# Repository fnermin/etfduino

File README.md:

MATLAB and Arduino to Acquire Analog Signals +15V/+15V

etfarduino

A project which allows the use of an Arduino device for data acquisition within the MATLAB Data Acquisition Toolbox.

A zip bundle containing the compiled x86 binaries and Arduino source can be downloaded from https://github.com/mlalic/etfarduino

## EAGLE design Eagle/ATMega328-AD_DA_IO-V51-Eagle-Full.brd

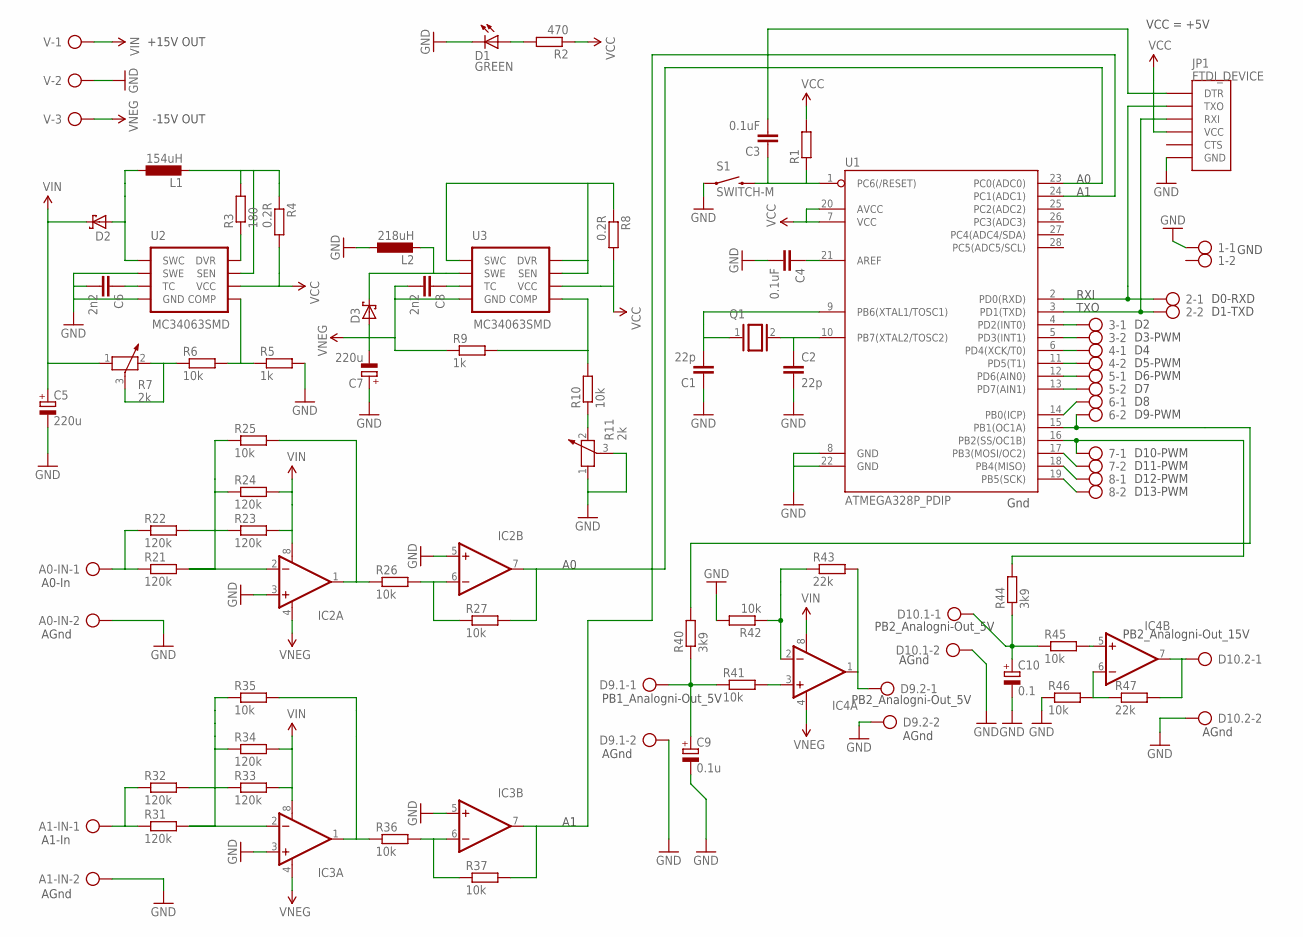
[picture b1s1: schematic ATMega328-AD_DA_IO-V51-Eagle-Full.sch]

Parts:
1, 2, 3, 4, 5, 6, 7, 8: AK500/2
A0-IN, A1-IN: AK500/2
C1, C2: 22p; C0805K
C3, C4: 0.1uF; C0805K
C5, C7: 220u; E3,5-10
C6, C8: 2n2; C0805K
C9: 0.1u; E2,5-5
C10: 0.1; E2,5-5
D1: GREEN; LED-1206
D2, D3: SCHOTTKY-DIODESMD; SMB
D9.1, D9.2, D10.1, D10.2: AK500/2
IC2, IC3, IC4: OPAMP-DUALU; SO08
JP1: FTDI_DEVICE; FTDI_DEVICE_SIDE
L1: 154uH; 0207/2V
L2: 218uH; 0207/2V
Q1: XTAL/S; QS
R1: R-EU_M0805; M0805
R2: 470; M0805
R3: 180; M0805
R4, R8: 0.2R; 0411/12
R5, R9: 1k; M0805
R6, R10, R25, R26, R27, R35, R36, R37, R41, R42, R45, R46: 10k; M0805
R7, R11: 2k; PT-10S
R21, R22, R23, R24, R31, R32, R33, R34: 120k; M0805
R40, R44: 3k9; M0805
R43, R47: 22k; M0805
S1: SWITCH-M; TACTILE-PTH
U1: ATMEGA328P_PDIP; DIL28-3
U2, U3: MC34063SMD; SO08
V: AK500/3

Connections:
GND: 1.1, A0-IN.2, A1-IN.2, C1.1, C2.2, C4.2, C5.-, C6.2, C7.+, C9.-, C10.-, D1.C, D9.1.2, D9.2.2, D10.1.2, D10.2.2, IC2.3 (+IN), IC2.5 (+IN), IC3.3 (+IN), IC3.5 (+IN), JP1.P$6 (GND), L2.1, R5.2, R11.1, R11.3, R42.2, R46.1, S1.1, U1.8 (GND), U1.22 (GND), U2.2 (SWE), U2.4 (GND), V.2
unnamed: R3.1, U2.8 (DVR)
unnamed: D2.A, L1.1, U2.1 (SWC)
unnamed: L1.2, R3.2, R4.1, U2.7 (SEN)
unnamed: D1.A, R2.2
unnamed: IC4.5 (+IN), R45.2
unnamed: C9.+, D9.1.1, R40.1, R41.1
unnamed: C10.+, D10.1.1, R44.1, R45.1
unnamed: IC4.3 (+IN), R41.2
unnamed: IC4.2 (-IN), R42.1, R43.1
unnamed: 6.2, R40.2, U1.15 (PB1(OC1A))
unnamed: D9.2.1, IC4.1 (OUT), R43.2
unnamed: 8.1, U1.18 (PB4(MISO))
unnamed: IC4.6 (-IN), R46.2, R47.1
unnamed: 7.1, R44.2, U1.16 (PB2(SS/OC1B))
unnamed: 8.2, U1.19 (PB5(SCK))
unnamed: R5.1, R6.2, U2.5 (COMP)
unnamed: C6.1, U2.3 (TC)
unnamed: A1-IN.1, R31.1, R32.1
unnamed: R6.1, R7.2, R7.3
unnamed: A0-IN.1, R21.1, R22.1
unnamed: IC2.2 (-IN), R21.2, R22.2, R23.1, R24.1, R25.1
unnamed: IC2.1 (OUT), R25.2, R26.1
unnamed: IC2.6 (-IN), R26.2, R27.1
unnamed: IC3.2 (-IN), R31.2, R32.2, R33.1, R34.1, R35.1
unnamed: IC3.1 (OUT), R35.2, R36.1
unnamed: IC3.6 (-IN), R36.2, R37.1
unnamed: D10.2.1, IC4.7 (OUT), R47.2
unnamed: C8.1, U3.3 (TC)
unnamed: 3.1, U1.4 (PD2(INT0))
unnamed: D3.C, L2.2, U3.2 (SWE)
unnamed: R10.1, R11.2
unnamed: IC2.7 (OUT), R27.2, U1.23 (PC0(ADC0))
unnamed: C3.1, R1.1, S1.3 (2), U1.1 (PC6(/RESET))
unnamed: C2.1, Q1.2, U1.10 (PB7(XTAL2/TOSC2))
unnamed: C3.2, JP1.P$1 (DTR)
unnamed: C4.1, U1.21 (AREF)
unnamed: 2.1, JP1.P$2 (TXO), U1.2 (PD0(RXD))
unnamed: C1.2, Q1.1, U1.9 (PB6(XTAL1/TOSC1))
unnamed: 2.2, JP1.P$3 (RXI), U1.3 (PD1(TXD))
unnamed: 3.2, U1.5 (PD3(INT1))
unnamed: IC3.7 (OUT), R37.2, U1.24 (PC1(ADC1))
unnamed: 4.1, U1.6 (PD4(XCK/T0))
unnamed: 4.2, U1.11 (PD5(T1))
unnamed: R9.2, R10.2, U3.5 (COMP)
unnamed: 5.1, U1.12 (PD6(AIN0))
unnamed: 5.2, U1.13 (PD7(AIN1))
unnamed: 6.1, U1.14 (PB0(ICP))
unnamed: R8.1, U3.1 (SWC), U3.7 (SEN), U3.8 (DVR)
unnamed: 7.2, U1.17 (PB3(MOSI/OC2))
VCC: JP1.P$4 (VCC), R1.2, R2.1, R4.2, R8.2, U1.7 (VCC), U1.20 (AVCC), U2.6 (VCC), U3.6 (VCC)
VIN: C5.+, D2.C, IC2.8 (V+), IC3.8 (V+), IC4.8 (V+), R7.1, R23.2, R24.2, R33.2, R34.2, V.1
VNEG: C7.-, C8.2, D3.A, IC2.4 (V-), IC3.4 (V-), IC4.4 (V-), R9.1, U3.4 (GND), V.3

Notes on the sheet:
-15V OUT
RXI
TXO
+15V OUT
VCC = +5V
A0-In
AGnd
A1-In
PB1_Analogni-Out_5V
PB2_Analogni-Out_5V
PB2_Analogni-Out_15V
D13-PWM
Gnd
D12-PWM
GND
D11-PWM
D10-PWM
D9-PWM
D6-PWM
D5-PWM
D3-PWM
D1-TXD
D0-RXD

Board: 2 copper layers, 72 parts (0 on the bottom side), 53 nets, no tracks yet.

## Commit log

2017-02-01 Create sch

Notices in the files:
parts and their libraries:
SparkFun-Connectors: Licensing: CC v3.0 Share-Alike You are welcome to use this library for commercial purposes.
